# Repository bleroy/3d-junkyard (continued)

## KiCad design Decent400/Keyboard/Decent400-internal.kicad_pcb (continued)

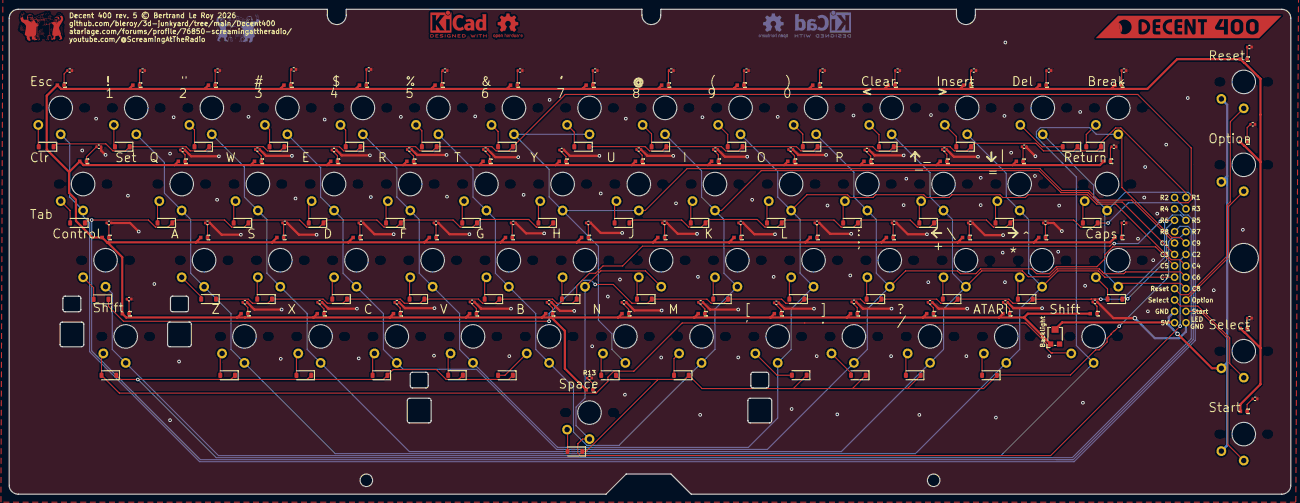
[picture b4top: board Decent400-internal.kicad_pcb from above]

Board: 2 copper layers, 286.0 x 108.2 mm, 180 parts (1 on the bottom side), 142 nets.

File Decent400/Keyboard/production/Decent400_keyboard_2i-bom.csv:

Designator,Footprint,Quantity,Value,LCSC Part #
"D1, D10, D11, D12, D13, D14, D15, D16, D17, D18, D19, D2, D20, D21, D22, D23, D24, D25, D26, D27, D28, D29, D3, D30, D31, D32, D33, D34, D35, D36, D37, D38, D39, D4, D40, D41, D42, D43, D44, D45, D46, D47, D48, D49, D5, D50, D51, D52, D53, D54, D55, D56, D6, D7, D8, D9",D_SOD-123,56,1N4148W,C81598
J1,PinHeader_1x22_P2.54mm_Vertical,1,Conn_01x22,
"R1, R10, R11, R12, R13, R14, R15, R16, R17, R18, R19, R2, R20, R21, R22, R23, R24, R25, R26, R27, R28, R29, R3, R30, R31, R32, R33, R34, R35, R36, R37, R38, R39, R4, R40, R41, R42, R43, R44, R45, R46, R47, R48, R49, R5, R50, R51, R52, R53, R54, R55, R56, R57, R58, R6, R61, R62, R63, R64, R7, R8, R9",0603,62,100,C22775
RV1,Potentiometer_Bourns_TC33X_Vertical,1,R_Potentiometer,C720647
SW0,MX-1-00U-LED-UPSIDE-DOWN,1,0,C193191
SW1,MX-1-00U-LED-UPSIDE-DOWN,1,1,C193191
SW2,MX-1-00U-LED-UPSIDE-DOWN,1,2,C193191
SW3,MX-1-00U-LED-UPSIDE-DOWN,1,3,C193191
SW4,MX-1-00U-LED-UPSIDE-DOWN,1,4,C193191
SW5,MX-1-00U-LED-UPSIDE-DOWN,1,5,C193191
SW6,MX-1-00U-LED-UPSIDE-DOWN,1,6,C193191
SW7,MX-1-00U-LED-UPSIDE-DOWN,1,7,C193191
SW8,MX-1-00U-LED-UPSIDE-DOWN,1,8,C193191
SW9,MX-1-00U-LED-UPSIDE-DOWN,1,9,C193191
SWA1,MX-1-00U-LED-UPSIDE-DOWN,1,A,C193191
SWB1,MX-1-00U-LED-UPSIDE-DOWN,1,B,C193191
SWBrk1,MX-1-25U-LED-REVERSED,1,Break,C193191
SWC1,MX-1-00U-LED-UPSIDE-DOWN,1,C,C193191
SWComma1,MX-1-00U-LED-UPSIDE-DOWN,1,Comma,C193191
SWCps1,MX-1-00U-LED-UPSIDE-DOWN,1,Caps,C193191
"SWCtl1, SWCtl2",MX-1-25U-LED-REVERSED,2,Control,C193191
SWD1,MX-1-00U-LED-UPSIDE-DOWN,1,D,C193191
SWDash1,MX-1-00U-LED-UPSIDE-DOWN,1,Dash,C193191
SWDel1,MX-1-75U-LED-REVERSED,1,Del,C193191
SWE1,MX-1-00U-LED-UPSIDE-DOWN,1,E,C193191
SWEqual1,MX-1-00U-LED-UPSIDE-DOWN,1,Equal,C193191
SWEsc1,MX-1-25U-LED-REVERSED,1,Esc,C193191
SWF1,MX-1-00U-LED-UPSIDE-DOWN,1,F,C193191
SWG1,MX-1-00U-LED-UPSIDE-DOWN,1,G,C193191
SWGT1,MX-1-00U-LED-UPSIDE-DOWN,1,GreaterThan,C193191
SWH1,MX-1-00U-LED-UPSIDE-DOWN,1,H,C193191
SWI1,MX-1-00U-LED-UPSIDE-DOWN,1,I,C193191
SWInv1,MX-1-00U-LED-UPSIDE-DOWN,1,Atari,C193191
SWJ1,MX-1-00U-LED-UPSIDE-DOWN,1,J,C193191
SWK1,MX-1-00U-LED-UPSIDE-DOWN,1,K,C193191
SWL1,MX-1-00U-LED-UPSIDE-DOWN,1,L,C193191
SWLT1,MX-1-00U-LED-UPSIDE-DOWN,1,LessThan,C193191
SWLeftSft1,MX-1-25U-LED-REVERSED,1,Shift,C193191
SWM1,MX-1-00U-LED-UPSIDE-DOWN,1,M,C193191
SWN1,MX-1-00U-LED-UPSIDE-DOWN,1,N,C193191
SWO1,MX-1-00U-LED-UPSIDE-DOWN,1,O,C193191
SWOption1,MX-1-00U-LED,1,Option,C193191
SWP1,MX-1-00U-LED-UPSIDE-DOWN,1,P,C193191
SWPeriod1,MX-1-00U-LED-UPSIDE-DOWN,1,Period,C193191
SWPlus1,MX-1-00U-LED-UPSIDE-DOWN,1,Plus,C193191
SWQ1,MX-1-00U-LED-UPSIDE-DOWN,1,Q,C193191
SWR1,MX-1-00U-LED-UPSIDE-DOWN,1,R,C193191
SWReset1,MX-1-00U-LED,1,Reset,C193191
SWRet1,MX-1-25U-LED-REVERSED,1,Return,C193191
SWRightSft1,MX-2-25U-LED-REVERSED,1,Shift,C193191
SWS1,MX-1-00U-LED-UPSIDE-DOWN,1,S,C193191
SWSelect1,MX-1-00U-LED,1,Select,C193191
SWSemi1,MX-1-00U-LED-UPSIDE-DOWN,1,Semicolon,C193191
SWSlash1,MX-1-00U-LED-UPSIDE-DOWN,1,Slash,C193191
SWSpc1,MX-6-25U-LED-REVERSED,1,Space,C193191
SWStar1,MX-1-00U-LED-UPSIDE-DOWN,1,Star,C193191
SWStart1,MX-1-00U-LED,1,Start,C193191
SWT1,MX-1-00U-LED-UPSIDE-DOWN,1,T,C193191
SWTab1,MX-1-25U-LED-REVERSED,1,Tab,C193191
SWU1,MX-1-00U-LED-UPSIDE-DOWN,1,U,C193191
SWV1,MX-1-00U-LED-UPSIDE-DOWN,1,V,C193191
SWW1,MX-1-00U-LED-UPSIDE-DOWN,1,W,C193191
SWX1,MX-1-00U-LED-UPSIDE-DOWN,1,X,C193191
SWY1,MX-1-00U-LED-UPSIDE-DOWN,1,Y,C193191
SWZ1,MX-1-00U-LED-UPSIDE-DOWN,1,Z,C193191

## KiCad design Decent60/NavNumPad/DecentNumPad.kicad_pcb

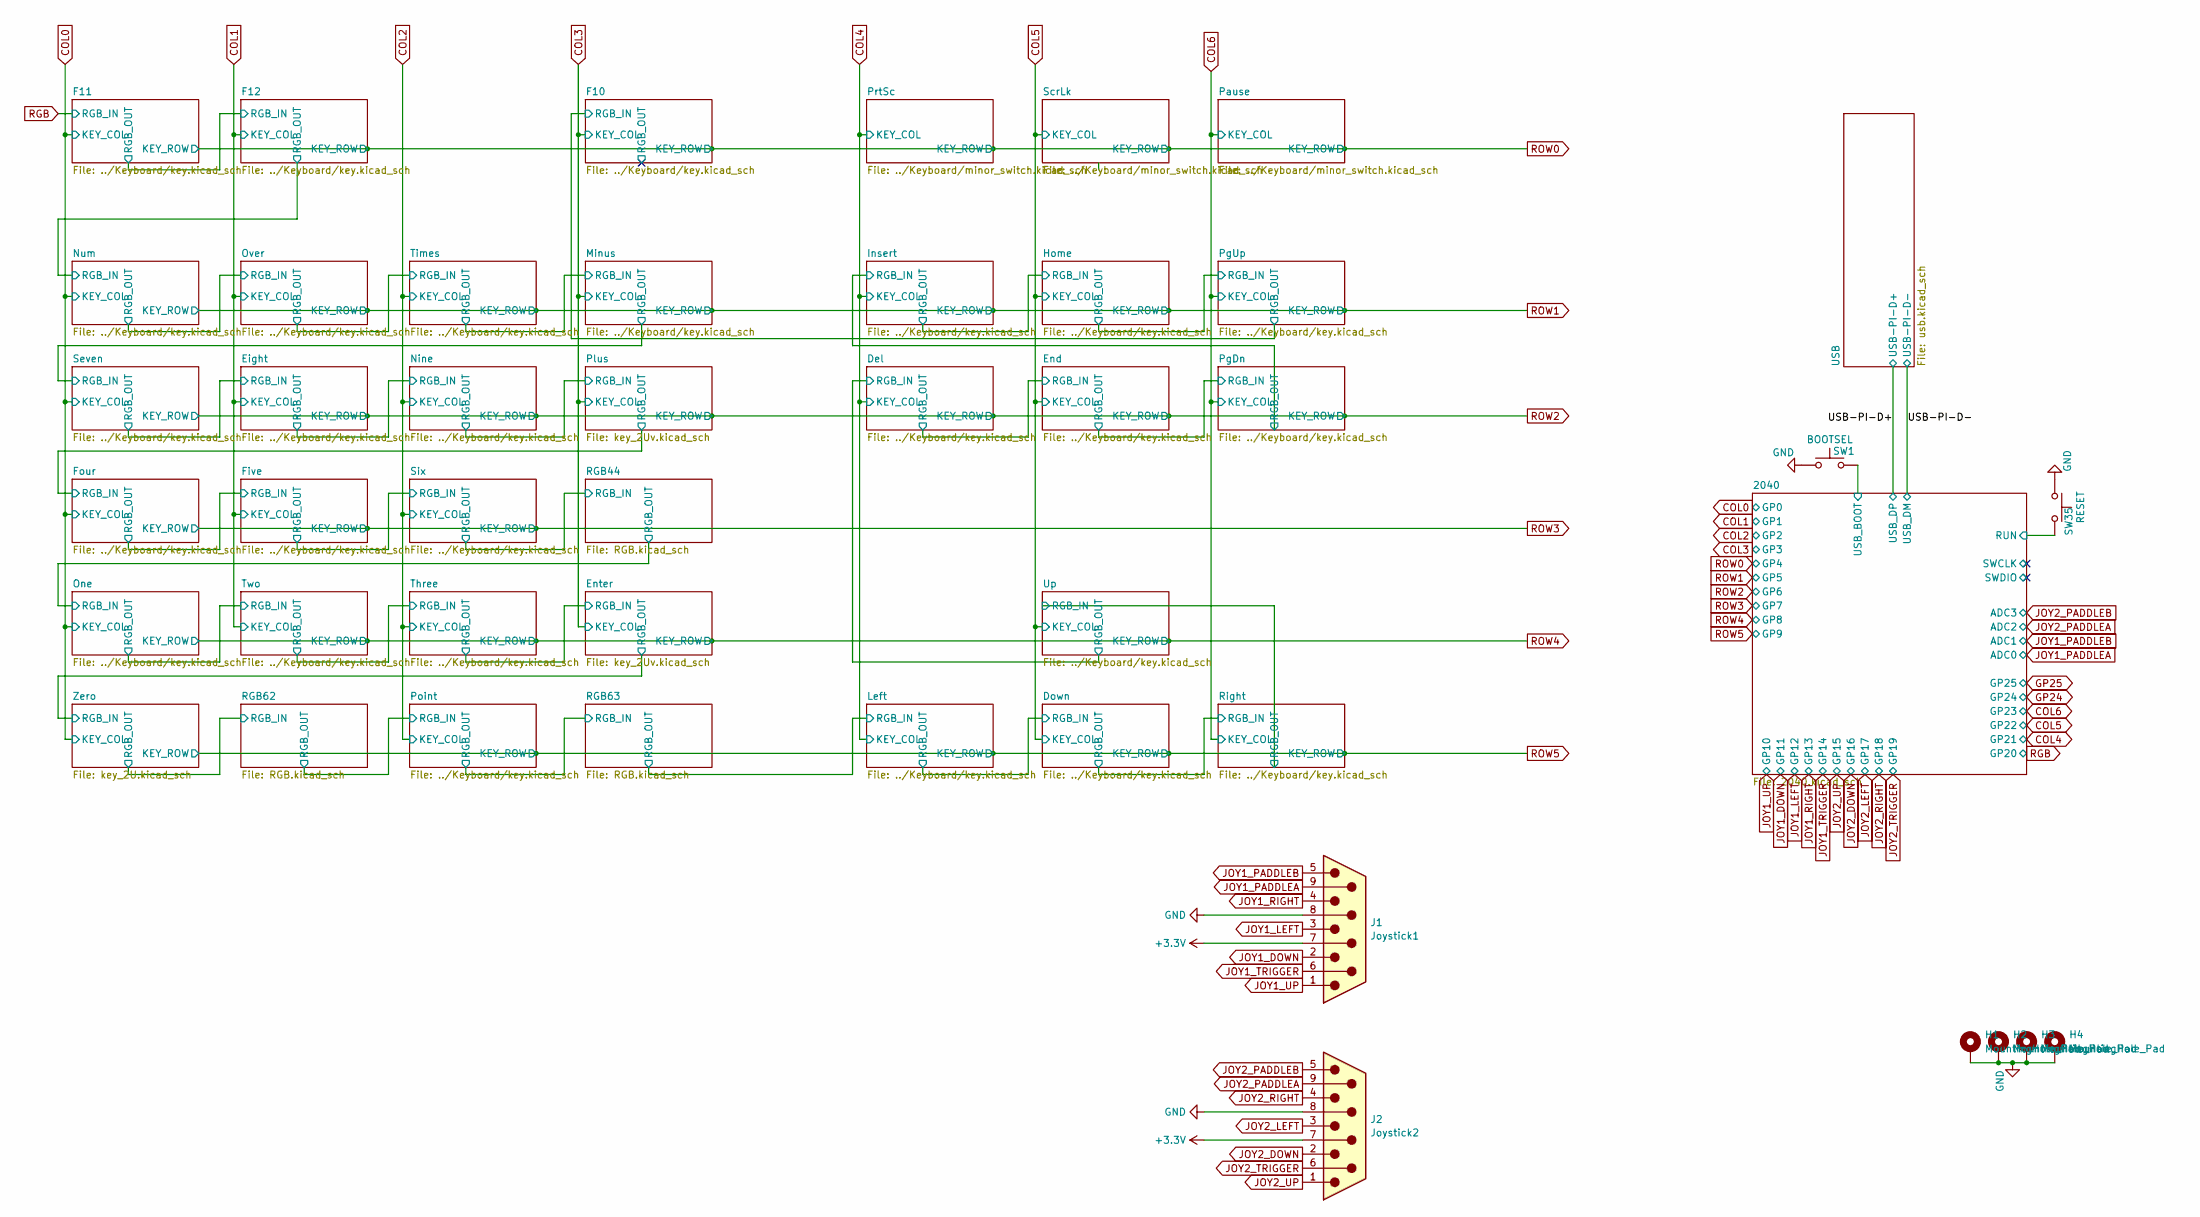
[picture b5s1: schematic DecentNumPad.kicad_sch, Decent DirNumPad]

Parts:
H1, H2, H3, H4: MountingHole_Pad; MountingHole_2.5mm_Pad_Via
J1: Joystick1; DSUB-9_Pins_Horizontal_P2.77x2.84mm_EdgePinOffset4.94mm_Hou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
J2: Joystick2; DSUB-9_Pins_Horizontal_P2.77x2.84mm_EdgePinOffset4.94mm_Hou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
SW1: BOOTSEL; SW-SMD_L3.9-W3.0-P4.45; LCSC Part # C720477
SW35: RESET; SW-SMD_L3.9-W3.0-P4.45; LCSC Part # C720477

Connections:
+3.3V: J1.7, J2.7; also elsewhere on the board
/2040/RUN: SW35.2; also elsewhere on the board
/2040/USB_BOOT: SW1.2; also elsewhere on the board
GND: H1.1 (1_1), H2.1 (1_1), H3.1 (1_1), H4.1 (1_1), J1.8, J2.8, SW1.1, SW35.1; also elsewhere on the board
JOY1_DOWN: J1.2; also elsewhere on the board
JOY1_LEFT: J1.3; also elsewhere on the board
JOY1_PADDLEA: J1.9; also elsewhere on the board
JOY1_PADDLEB: J1.5; also elsewhere on the board
JOY1_RIGHT: J1.4; also elsewhere on the board
JOY1_TRIGGER: J1.6; also elsewhere on the board
JOY1_UP: J1.1; also elsewhere on the board
JOY2_DOWN: J2.2; also elsewhere on the board
JOY2_LEFT: J2.3; also elsewhere on the board
JOY2_PADDLEA: J2.9; also elsewhere on the board
JOY2_PADDLEB: J2.5; also elsewhere on the board
JOY2_RIGHT: J2.4; also elsewhere on the board
JOY2_TRIGGER: J2.6; also elsewhere on the board
JOY2_UP: J2.1; also elsewhere on the board

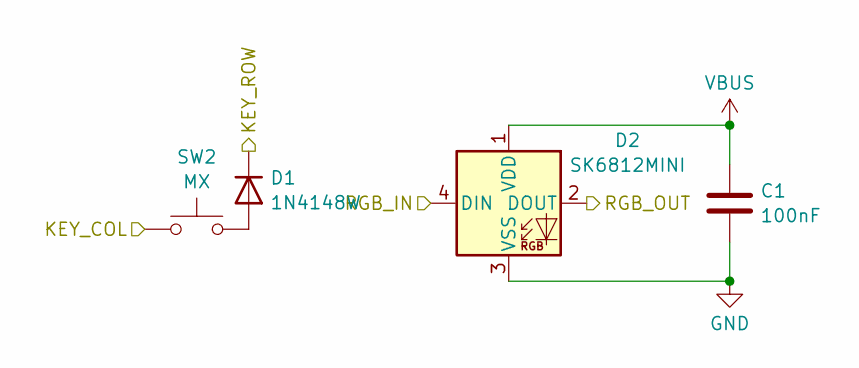
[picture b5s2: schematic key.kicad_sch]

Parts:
C1: 100nF; C_0402_1005Metric; LCSC Part # C1525
D1: 1N4148W; D_SOD-123; LCSC Part # C81598
D2: SK6812MINI; LED_SK6812MINI-E_3.2x2.8mm_P1.5mm_ReverseMount; LCSC Part # C5378731
SW2: MX; SMD_KEYBOARD-SW; LCSC Part # C41430893

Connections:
/F11/RGB_OUT: D2.2 (DOUT); also elsewhere on the board
COL0: SW2.1; also elsewhere on the board
GND: C1.2, D2.3 (VSS); also elsewhere on the board
unnamed: D1.2 (A), SW2.2
RGB: D2.4 (DIN); also elsewhere on the board
ROW0: D1.1 (K); also elsewhere on the board
VBUS: C1.1, D2.1 (VDD); also elsewhere on the board

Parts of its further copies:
C2, C3, C4, C5, C6, C8, C9, C10, C11, C12, C13, C14, C15, C17, C19, C45, C46, C47, C48, C49, C50, C53, C54, C55, C56, C57: 100nF; C_0402_1005Metric; LCSC Part # C1525
D3, D5, D7, D9, D11, D15, D17, D19, D21, D23, D25, D27, D29, D33, D37, D44, D46, D48, D50, D52, D54, D60, D62, D64, D66, D68: 1N4148W; D_SOD-123; LCSC Part # C81598
D4, D6, D8, D10, D12, D16, D18, D20, D22, D24, D26, D28, D30, D34, D38, D45, D47, D49, D51, D53, D55, D61, D63, D65, D67, D69: SK6812MINI; LED_SK6812MINI-E_3.2x2.8mm_P1.5mm_ReverseMount; LCSC Part # C5378731
SW3, SW4, SW5, SW6, SW7, SW9, SW10, SW11, SW12, SW13, SW14, SW15, SW16, SW18, SW20, SW22, SW23, SW24, SW25, SW26, SW27, SW30, SW31, SW32, SW33, SW34: MX; SMD_KEYBOARD-SW; LCSC Part # C41430893

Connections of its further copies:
/Del/RGB_IN: D51.2 (DOUT), D67.4 (DIN)
/Del/RGB_OUT: D65.4 (DIN), D67.2 (DOUT)
/Down/RGB_IN: D45.2 (DOUT), D47.4 (DIN)
/Down/RGB_OUT: D47.2 (DOUT), D49.4 (DIN)
/Eight/RGB_IN: D16.2 (DOUT), D18.4 (DIN)
/Eight/RGB_OUT: D18.2 (DOUT), D20.4 (DIN)
/End/RGB_OUT: D65.2 (DOUT), D69.4 (DIN)
/Enter/RGB_IN: D30.2 (DOUT); also elsewhere on the board
/F10/RGB_IN: D61.2 (DOUT), D63.4 (DIN)
/F10/RGB_OUT: D63.2 (DOUT)
/F11/RGB_OUT: D4.4 (DIN); also elsewhere on the board
/F12/RGB_OUT: D4.2 (DOUT), D6.4 (DIN)
/Five/RGB_IN: D22.4 (DIN), D28.2 (DOUT)
/Five/RGB_OUT: D22.2 (DOUT), D24.4 (DIN)
/Four/RGB_IN: D28.4 (DIN); also elsewhere on the board
/Home/RGB_IN: D53.2 (DOUT), D55.4 (DIN)
/Home/RGB_OUT: D55.2 (DOUT), D61.4 (DIN)
/Insert/RGB_IN: D53.4 (DIN), D69.2 (DOUT)
/Left/RGB_IN: D45.4 (DIN); also elsewhere on the board
/Minus/RGB_IN: D10.2 (DOUT), D12.4 (DIN)
/Minus/RGB_OUT: D12.2 (DOUT), D16.4 (DIN)
/Nine/RGB_OUT: D20.2 (DOUT); also elsewhere on the board
/Num/RGB_OUT: D6.2 (DOUT), D8.4 (DIN)
/One/RGB_IN: D34.4 (DIN); also elsewhere on the board
/One/RGB_OUT: D26.4 (DIN), D34.2 (DOUT)
/Over/RGB_OUT: D8.2 (DOUT), D10.4 (DIN)
/Point/RGB_IN: D38.4 (DIN); also elsewhere on the board
/Point/RGB_OUT: D38.2 (DOUT); also elsewhere on the board
/RGB44/RGB_IN: D24.2 (DOUT); also elsewhere on the board
/Right/RGB_OUT: D49.2 (DOUT), D51.4 (DIN)
/Three/RGB_IN: D26.2 (DOUT), D30.4 (DIN)
COL0: SW4.1, SW9.1, SW15.1, SW18.1; also elsewhere on the board
COL1: SW3.1, SW5.1, SW10.1, SW12.1, SW14.1; also elsewhere on the board
COL2: SW6.1, SW11.1, SW13.1, SW16.1, SW20.1; also elsewhere on the board
COL3: SW7.1, SW31.1; also elsewhere on the board
COL4: SW22.1, SW26.1, SW33.1; also elsewhere on the board
COL5: SW23.1, SW25.1, SW27.1, SW32.1; also elsewhere on the board
COL6: SW24.1, SW30.1, SW34.1; also elsewhere on the board
GND: C2.2, C3.2, C4.2, C5.2, C6.2, C8.2, C9.2, C10.2, C11.2, C12.2, C13.2, C14.2, C15.2, C17.2, C19.2, C45.2, C46.2, C47.2, C48.2, C49.2, C50.2, C53.2, C54.2, C55.2, C56.2, C57.2, D4.3 (VSS), D6.3 (VSS), D8.3 (VSS), D10.3 (VSS), D12.3 (VSS), D16.3 (VSS), D18.3 (VSS), D20.3 (VSS), D22.3 (VSS), D24.3 (VSS), D26.3 (VSS), D28.3 (VSS), D30.3 (VSS), D34.3 (VSS), D38.3 (VSS), D45.3 (VSS), D47.3 (VSS), D49.3 (VSS), D51.3 (VSS), D53.3 (VSS), D55.3 (VSS), D61.3 (VSS), D63.3 (VSS), D65.3 (VSS), D67.3 (VSS), D69.3 (VSS); also elsewhere on the board
unnamed: D3.2 (A), SW3.2
unnamed: D5.2 (A), SW4.2
unnamed: D7.2 (A), SW5.2
unnamed: D9.2 (A), SW6.2
unnamed: D11.2 (A), SW7.2
unnamed: D15.2 (A), SW9.2
unnamed: D17.2 (A), SW10.2
unnamed: D19.2 (A), SW11.2
unnamed: D21.2 (A), SW12.2
unnamed: D23.2 (A), SW13.2
unnamed: D25.2 (A), SW14.2
unnamed: D27.2 (A), SW15.2
unnamed: D29.2 (A), SW16.2
unnamed: D33.2 (A), SW18.2
unnamed: D37.2 (A), SW20.2
unnamed: D44.2 (A), SW22.2
unnamed: D46.2 (A), SW23.2
unnamed: D48.2 (A), SW24.2
unnamed: D50.2 (A), SW25.2
unnamed: D52.2 (A), SW26.2
unnamed: D54.2 (A), SW27.2
unnamed: D60.2 (A), SW30.2
unnamed: D62.2 (A), SW31.2
unnamed: D64.2 (A), SW32.2
unnamed: D66.2 (A), SW33.2
unnamed: D68.2 (A), SW34.2
ROW0: D3.1 (K), D62.1 (K); also elsewhere on the board
ROW1: D5.1 (K), D7.1 (K), D9.1 (K), D11.1 (K), D52.1 (K), D54.1 (K), D60.1 (K); also elsewhere on the board
ROW2: D15.1 (K), D17.1 (K), D19.1 (K), D64.1 (K), D66.1 (K), D68.1 (K); also elsewhere on the board
ROW3: D21.1 (K), D23.1 (K), D27.1 (K); also elsewhere on the board
ROW4: D25.1 (K), D29.1 (K), D33.1 (K), D50.1 (K); also elsewhere on the board
ROW5: D37.1 (K), D44.1 (K), D46.1 (K), D48.1 (K); also elsewhere on the board
VBUS: C2.1, C3.1, C4.1, C5.1, C6.1, C8.1, C9.1, C10.1, C11.1, C12.1, C13.1, C14.1, C15.1, C17.1, C19.1, C45.1, C46.1, C47.1, C48.1, C49.1, C50.1, C53.1, C54.1, C55.1, C56.1, C57.1, D4.1 (VDD), D6.1 (VDD), D8.1 (VDD), D10.1 (VDD), D12.1 (VDD), D16.1 (VDD), D18.1 (VDD), D20.1 (VDD), D22.1 (VDD), D24.1 (VDD), D26.1 (VDD), D28.1 (VDD), D30.1 (VDD), D34.1 (VDD), D38.1 (VDD), D45.1 (VDD), D47.1 (VDD), D49.1 (VDD), D51.1 (VDD), D53.1 (VDD), D55.1 (VDD), D61.1 (VDD), D63.1 (VDD), D65.1 (VDD), D67.1 (VDD), D69.1 (VDD); also elsewhere on the board

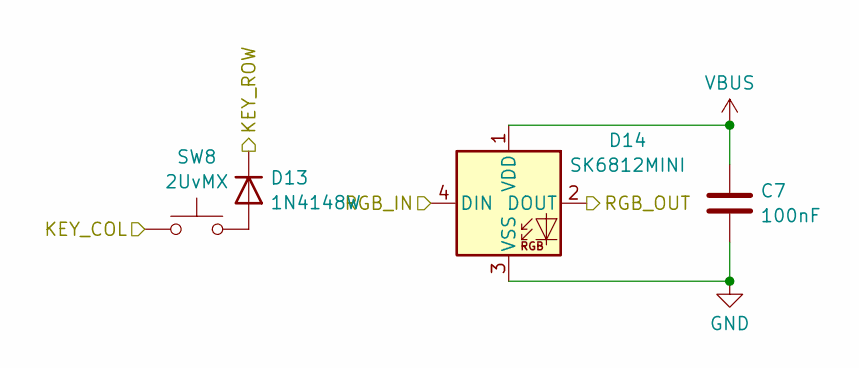
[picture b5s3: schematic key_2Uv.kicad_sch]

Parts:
C7: 100nF; C_0402_1005Metric; LCSC Part # C1525
D13: 1N4148W; D_SOD-123; LCSC Part # C81598
D14: SK6812MINI; LED_SK6812MINI-E_3.2x2.8mm_P1.5mm_ReverseMount; LCSC Part # C5378731
SW8: 2UvMX; Kailh_socket_MX_2-00U_V; LCSC Part # C41430893

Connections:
/Four/RGB_IN: D14.2 (DOUT); also elsewhere on the board
/Nine/RGB_OUT: D14.4 (DIN); also elsewhere on the board
COL3: SW8.1; also elsewhere on the board
GND: C7.2, D14.3 (VSS); also elsewhere on the board
unnamed: D13.2 (A), SW8.2
ROW2: D13.1 (K); also elsewhere on the board
VBUS: C7.1, D14.1 (VDD); also elsewhere on the board

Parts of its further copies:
C16: 100nF; C_0402_1005Metric; LCSC Part # C1525
D31: 1N4148W; D_SOD-123; LCSC Part # C81598
D32: SK6812MINI; LED_SK6812MINI-E_3.2x2.8mm_P1.5mm_ReverseMount; LCSC Part # C5378731
SW17: 2UvMX; Kailh_socket_MX_2-00U_V; LCSC Part # C41430893

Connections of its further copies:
/Enter/RGB_IN: D32.4 (DIN); also elsewhere on the board
/Enter/RGB_OUT: D32.2 (DOUT); also elsewhere on the board
COL3: SW17.1; also elsewhere on the board
GND: C16.2, D32.3 (VSS); also elsewhere on the board
unnamed: D31.2 (A), SW17.2
ROW4: D31.1 (K); also elsewhere on the board
VBUS: C16.1, D32.1 (VDD); also elsewhere on the board

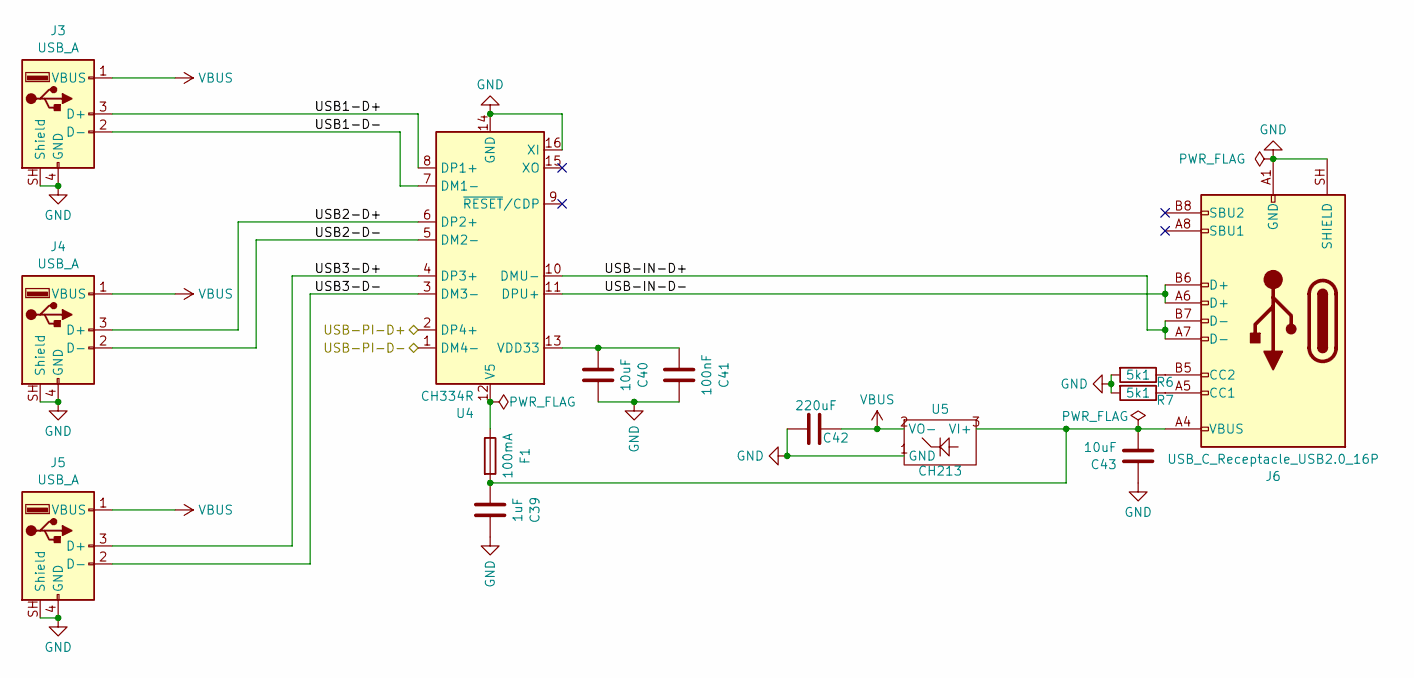
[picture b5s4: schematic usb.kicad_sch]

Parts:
C39: 1uF; C_0402_1005Metric; LCSC Part # C52923
C40, C43: 10uF; C_0402_1005Metric; LCSC Part # C15525
C41: 100nF; C_0402_1005Metric; LCSC Part # C1525
C42: 220uF; CP_Elec_6.3x5.4; LCSC Part # C3345
F1: 100mA; Fuse_1206_3216Metric; LCSC Part # C269108
J3, J4, J5: USB_A; USB_A_Molex_67643_Horizontal
J6: USB_C_Receptacle_USB2.0_16P; USB_C_Receptacle_HCTL_HC-TYPE-C-16P-01A; LCSC Part # C709357
R6, R7: 5k1; R_0402_1005Metric; LCSC Part # C25905
U4: CH334R; QSOP-16_3.9x4.9mm_P0.635mm; LCSC Part # C4154405
U5: CH213; TSOT-23; LCSC Part # C5456874

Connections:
/USB-PI-D+: U4.2 (DP4+); also elsewhere on the board
/USB-PI-D-: U4.1 (DM4-); also elsewhere on the board
/USB/USB1-D+: J3.3 (D+), U4.8 (DP1+)
/USB/USB1-D-: J3.2 (D-), U4.7 (DM1-)
/USB/USB2-D+: J4.3 (D+), U4.6 (DP2+)
/USB/USB2-D-: J4.2 (D-), U4.5 (DM2-)
/USB/USB3-D+: J5.3 (D+), U4.4 (DP3+)
/USB/USB3-D-: J5.2 (D-), U4.3 (DM3-)
/USB/USB-IN-D+: J6.A7 (D-), J6.B7 (D-), U4.10 (DMU-)
/USB/USB-IN-D-: J6.A6 (D+), J6.B6 (D+), U4.11 (DPU+)
GND: C39.2, C40.2, C41.2, C42.2, C43.1, J3.4 (GND), J3.SH (Shield), J4.4 (GND), J4.SH (Shield), J5.4 (GND), J5.SH (Shield), J6.A1 (GND), J6.A12 (GND), J6.B1 (GND), J6.B12 (GND), J6.SH (SHIELD), R6.2, R7.2, U4.14 (GND), U4.16 (XI), U5.1 (GND); also elsewhere on the board
unnamed: J6.A5 (CC1), R7.1
unnamed: J6.B5 (CC2), R6.1
unnamed: F1.1, U4.12 (V5)
unnamed: C40.1, C41.1, U4.13 (VDD33)
unnamed: C39.1, C43.2, F1.2, J6.A4 (VBUS), J6.A9 (VBUS), J6.B4 (VBUS), J6.B9 (VBUS), U5.3 (VI+)
VBUS: C42.1, J3.1 (VBUS), J4.1 (VBUS), J5.1 (VBUS), U5.2 (VO-); also elsewhere on the board

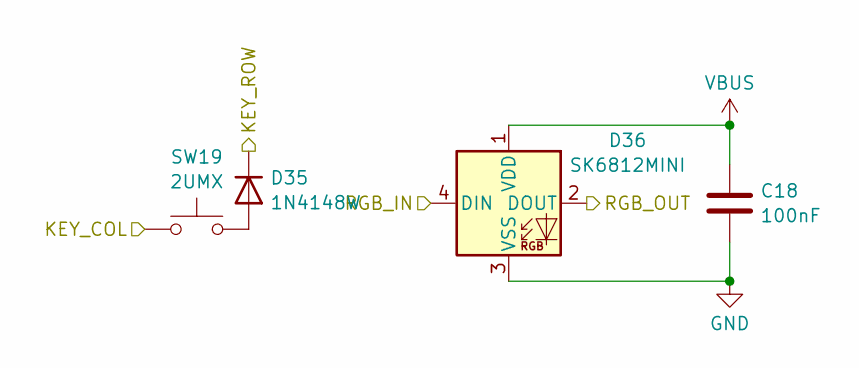
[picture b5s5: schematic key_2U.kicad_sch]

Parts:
C18: 100nF; C_0402_1005Metric; LCSC Part # C1525
D35: 1N4148W; D_SOD-123; LCSC Part # C81598
D36: SK6812MINI; LED_SK6812MINI-E_3.2x2.8mm_P1.5mm_ReverseMount; LCSC Part # C5378731
SW19: 2UMX; Kailh_socket_MX_2-00U; LCSC Part # C41430893

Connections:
/Enter/RGB_OUT: D36.4 (DIN); also elsewhere on the board
/RGB62/RGB_IN: D36.2 (DOUT); also elsewhere on the board
COL0: SW19.1; also elsewhere on the board
GND: C18.2, D36.3 (VSS); also elsewhere on the board
unnamed: D35.2 (A), SW19.2
ROW5: D35.1 (K); also elsewhere on the board
VBUS: C18.1, D36.1 (VDD); also elsewhere on the board

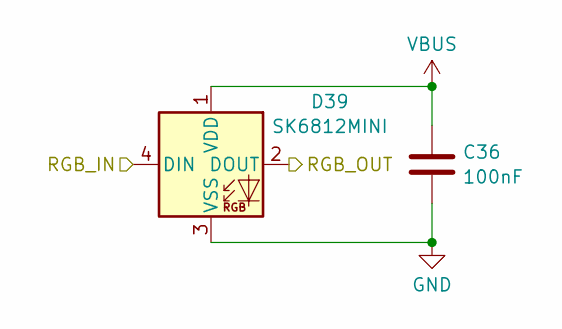
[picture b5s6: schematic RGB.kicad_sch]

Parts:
C36: 100nF; C_0402_1005Metric; LCSC Part # C1525
D39: SK6812MINI; LED_SK6812MINI-E_3.2x2.8mm_P1.5mm_ReverseMount; LCSC Part # C5378731

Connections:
/One/RGB_IN: D39.2 (DOUT); also elsewhere on the board
/RGB44/RGB_IN: D39.4 (DIN); also elsewhere on the board
GND: C36.2, D39.3 (VSS); also elsewhere on the board
VBUS: C36.1, D39.1 (VDD); also elsewhere on the board

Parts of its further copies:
C37, C38: 100nF; C_0402_1005Metric; LCSC Part # C1525
D40, D41: SK6812MINI; LED_SK6812MINI-E_3.2x2.8mm_P1.5mm_ReverseMount; LCSC Part # C5378731

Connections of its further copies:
/Left/RGB_IN: D41.2 (DOUT); also elsewhere on the board
/Point/RGB_IN: D40.2 (DOUT); also elsewhere on the board
/Point/RGB_OUT: D41.4 (DIN); also elsewhere on the board
/RGB62/RGB_IN: D40.4 (DIN); also elsewhere on the board
GND: C37.2, C38.2, D40.3 (VSS), D41.3 (VSS); also elsewhere on the board
VBUS: C37.1, C38.1, D40.1 (VDD), D41.1 (VDD); also elsewhere on the board

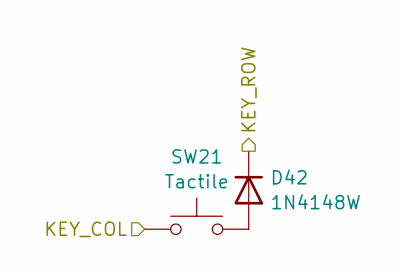
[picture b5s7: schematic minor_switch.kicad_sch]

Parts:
D42: 1N4148W; D_SOD-123; LCSC Part # C81598
SW21: Tactile; SMD_KEYBOARD-SW; LCSC Part # C41430893

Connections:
COL4: SW21.1; also elsewhere on the board
unnamed: D42.2 (A), SW21.2
ROW0: D42.1 (K); also elsewhere on the board

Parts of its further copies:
D56, D58: 1N4148W; D_SOD-123; LCSC Part # C81598
SW28, SW29: Tactile; SMD_KEYBOARD-SW; LCSC Part # C41430893

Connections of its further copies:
COL5: SW28.1; also elsewhere on the board
COL6: SW29.1; also elsewhere on the board
unnamed: D56.2 (A), SW28.2
unnamed: D58.2 (A), SW29.2
ROW0: D56.1 (K), D58.1 (K); also elsewhere on the board

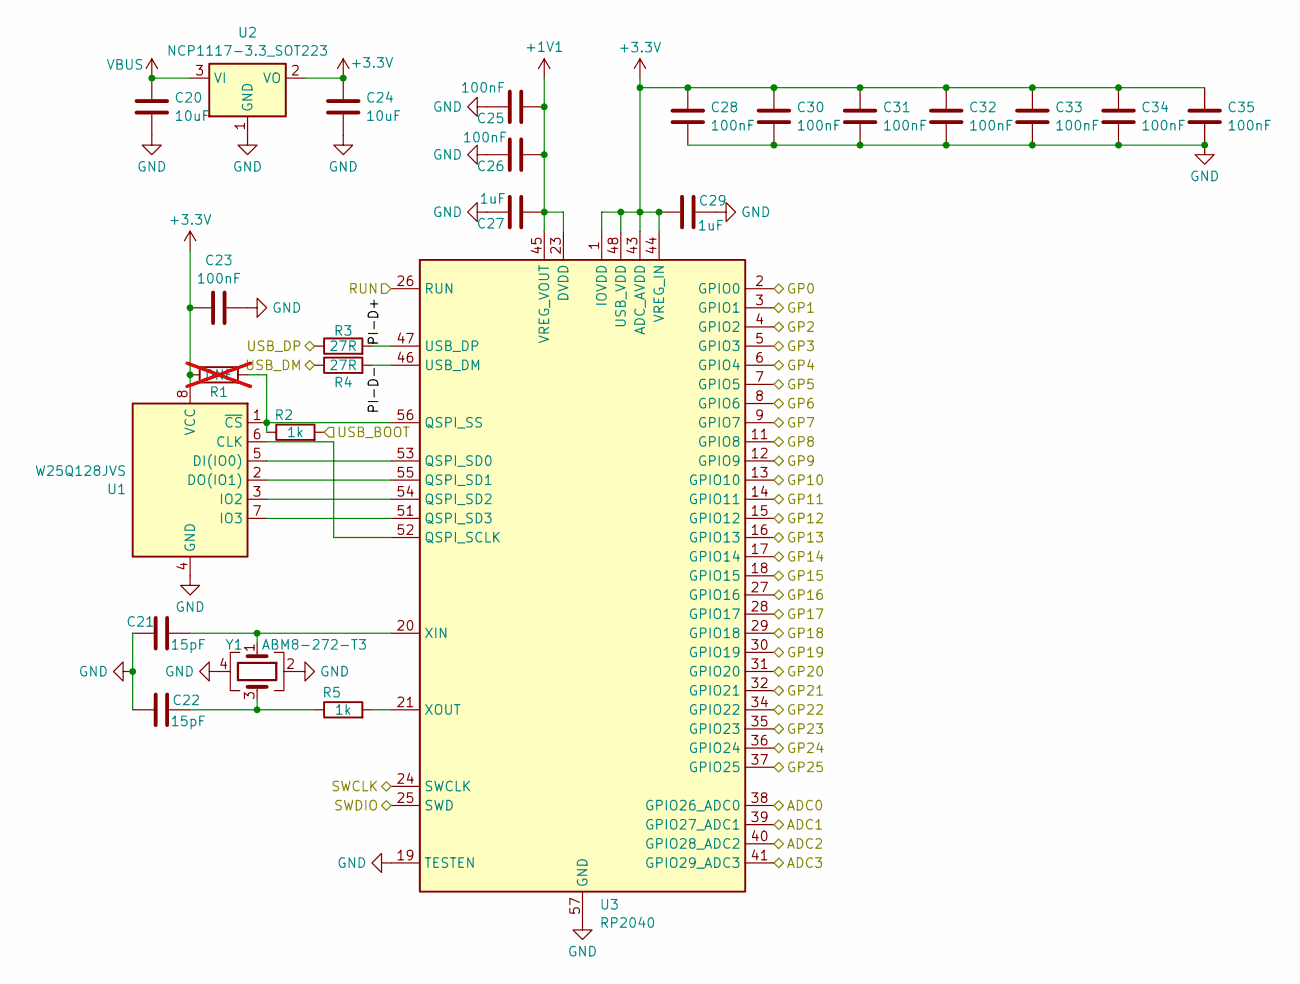
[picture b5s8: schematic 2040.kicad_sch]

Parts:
C20, C24: 10uF; C_0402_1005Metric; LCSC Part # C15525
C21, C22: 15pF; C_0402_1005Metric; LCSC Part # C1548
C23, C25, C26, C28, C30, C31, C32, C33, C34, C35: 100nF; C_0402_1005Metric; LCSC Part # C1525
C27, C29: 1uF; C_0402_1005Metric; LCSC Part # C52923
R1: DNF; R_0402_1005Metric; not fitted
R2, R5: 1k; R_0402_1005Metric; LCSC Part # C11702
R3, R4: 27R; R_0402_1005Metric; LCSC Part # C25100
U1: W25Q128JVS; SOIC-8_5.3x5.3mm_P1.27mm; LCSC Part # C97521
U2: NCP1117-3.3_SOT223; SOT-223-3_TabPin2; LCSC Part # C146799
U3: RP2040; QFN-56-1EP_7x7mm_P0.4mm_EP3.2x3.2mm; LCSC Part # C2040
Y1: ABM8-272-T3; Oscillator_SMD_Abracon_ASE-4Pin_3.2x2.5mm; LCSC Part # C20625731

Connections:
+1V1: C25.1, C26.1, C27.1, U3.23 (DVDD), U3.45 (VREG_VOUT), U3.50 (DVDD)
+3.3V: C23.2, C24.1, C28.1, C29.1, C30.1, C31.1, C32.1, C33.1, C34.1, C35.1, R1.1, U1.8 (VCC), U2.2 (VO), U3.1 (IOVDD), U3.10 (IOVDD), U3.22 (IOVDD), U3.33 (IOVDD), U3.42 (IOVDD), U3.43 (ADC_AVDD), U3.44 (VREG_IN), U3.48 (USB_VDD), U3.49 (IOVDD); also elsewhere on the board
/2040/PI-D+: R3.2, U3.47 (USB_DP)
/2040/PI-D-: R4.2, U3.46 (USB_DM)
/2040/RUN: U3.26 (RUN); also elsewhere on the board
/2040/SWCLK: U3.24 (SWCLK)
/2040/SWDIO: U3.25 (SWD)
/2040/USB_BOOT: R2.2; also elsewhere on the board
/USB-PI-D+: R3.1; also elsewhere on the board
/USB-PI-D-: R4.1; also elsewhere on the board
COL0: U3.2 (GPIO0); also elsewhere on the board
COL1: U3.3 (GPIO1); also elsewhere on the board
COL2: U3.4 (GPIO2); also elsewhere on the board
COL3: U3.5 (GPIO3); also elsewhere on the board
COL4: U3.32 (GPIO21); also elsewhere on the board
COL5: U3.34 (GPIO22); also elsewhere on the board
COL6: U3.35 (GPIO23); also elsewhere on the board
GND: C20.2, C21.1, C22.1, C23.1, C24.2, C25.2, C26.2, C27.2, C28.2, C29.2, C30.2, C31.2, C32.2, C33.2, C34.2, C35.2, U1.4 (GND), U2.1 (GND), U3.19 (TESTEN), U3.57 (GND), Y1.2, Y1.4; also elsewhere on the board
GP24: U3.36 (GPIO24)
GP25: U3.37 (GPIO25)
JOY1_DOWN: U3.14 (GPIO11); also elsewhere on the board
JOY1_LEFT: U3.15 (GPIO12); also elsewhere on the board
JOY1_PADDLEA: U3.38 (GPIO26_ADC0); also elsewhere on the board
JOY1_PADDLEB: U3.39 (GPIO27_ADC1); also elsewhere on the board
JOY1_RIGHT: U3.16 (GPIO13); also elsewhere on the board
JOY1_TRIGGER: U3.17 (GPIO14); also elsewhere on the board
JOY1_UP: U3.13 (GPIO10); also elsewhere on the board
JOY2_DOWN: U3.27 (GPIO16); also elsewhere on the board
JOY2_LEFT: U3.28 (GPIO17); also elsewhere on the board
JOY2_PADDLEA: U3.40 (GPIO28_ADC2); also elsewhere on the board
JOY2_PADDLEB: U3.41 (GPIO29_ADC3); also elsewhere on the board
JOY2_RIGHT: U3.29 (GPIO18); also elsewhere on the board
JOY2_TRIGGER: U3.30 (GPIO19); also elsewhere on the board
JOY2_UP: U3.18 (GPIO15); also elsewhere on the board
unnamed: C22.2, R5.1, Y1.3
unnamed: U1.6 (CLK), U3.52 (QSPI_SCLK)
unnamed: U1.5 (DI(IO0)), U3.53 (QSPI_SD0)
unnamed: U1.2 (DO(IO1)), U3.55 (QSPI_SD1)
unnamed: U1.3 (IO2), U3.54 (QSPI_SD2)
unnamed: U1.7 (IO3), U3.51 (QSPI_SD3)
unnamed: R1.2, R2.1, U1.1 (~CS), U3.56 (QSPI_SS)
unnamed: C21.2, U3.20 (XIN), Y1.1
unnamed: R5.2, U3.21 (XOUT)
RGB: U3.31 (GPIO20); also elsewhere on the board
ROW0: U3.6 (GPIO4); also elsewhere on the board
ROW1: U3.7 (GPIO5); also elsewhere on the board
ROW2: U3.8 (GPIO6); also elsewhere on the board
ROW3: U3.9 (GPIO7); also elsewhere on the board
ROW4: U3.11 (GPIO8); also elsewhere on the board
ROW5: U3.12 (GPIO9); also elsewhere on the board
VBUS: C20.1, U2.3 (VI); also elsewhere on the board

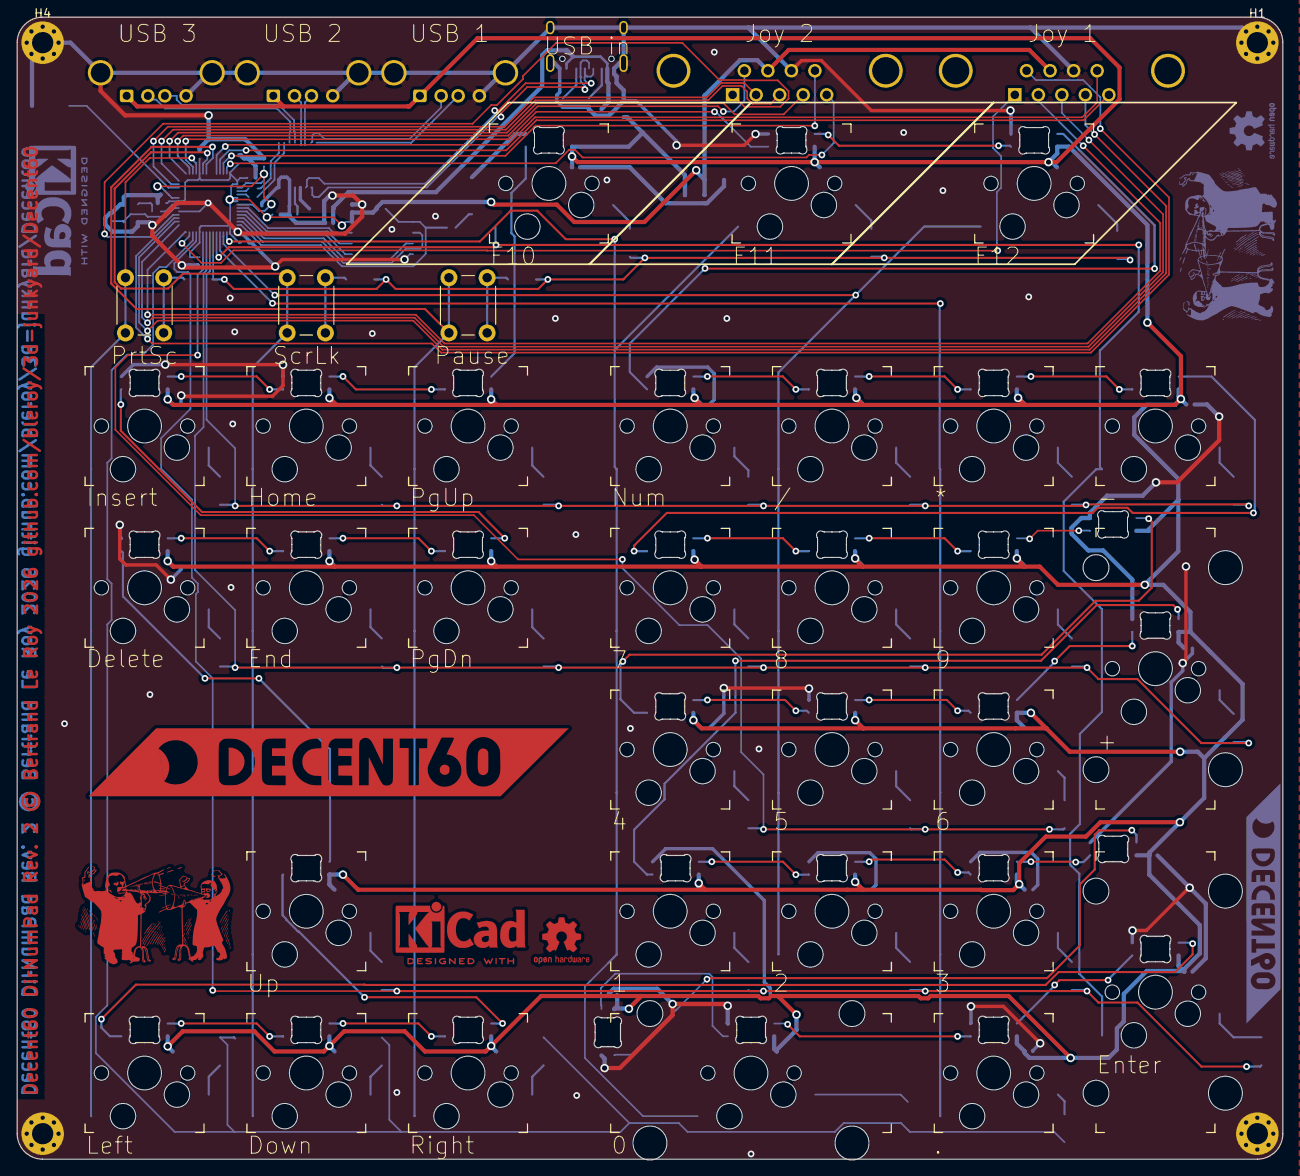
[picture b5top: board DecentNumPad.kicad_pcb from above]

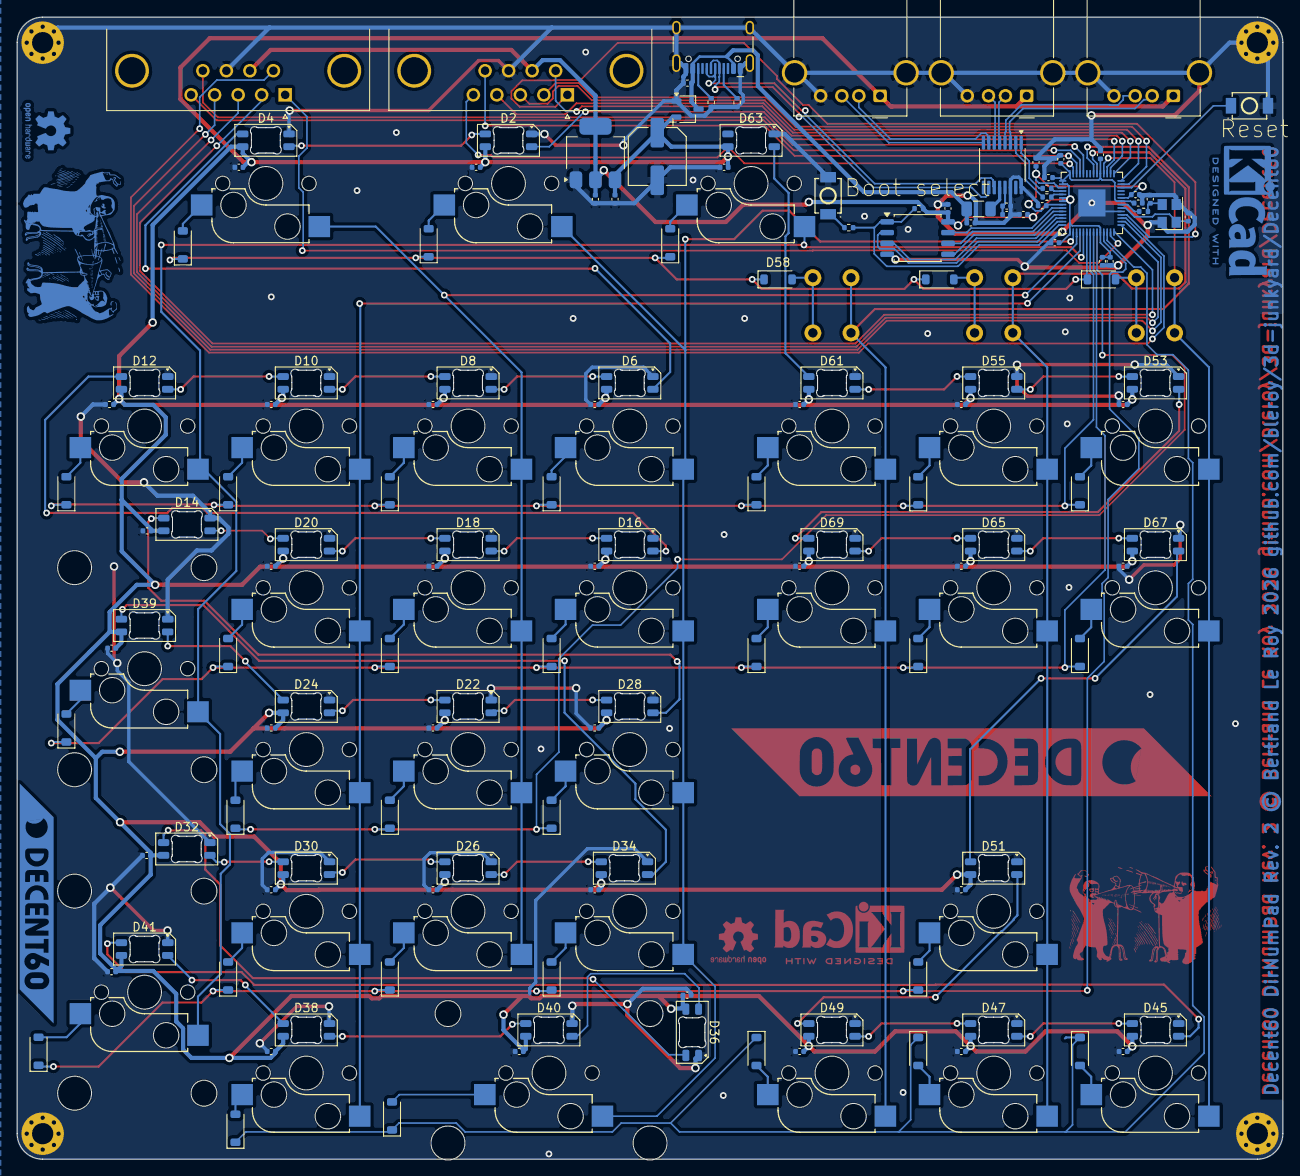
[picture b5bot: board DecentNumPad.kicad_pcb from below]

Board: 2 copper layers, 149.1 x 134.5 mm, 179 parts (142 on the bottom side), 125 nets.

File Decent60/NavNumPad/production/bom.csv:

Designator,Footprint,Quantity,Value,LCSC Part #
"C1, C10, C11, C12, C13, C14, C15, C16, C17, C18, C19, C2, C23, C25, C26, C28, C3, C30, C31, C32, C33, C34, C35, C36, C37, C38, C4, C41, C45, C46, C47, C48, C49, C5, C50, C53, C54, C55, C56, C57, C6, C7, C8, C9",0402,44,100nF,C1525
"C20, C24, C40, C43",0402,4,10uF,C15525
"C21, C22",0402,2,15pF,C1548
"C27, C29, C39",0402,3,1uF,C52923
C42,CP_Elec_6.3x5.4,1,220uF,C3345
"D1, D11, D13, D15, D17, D19, D21, D23, D25, D27, D29, D3, D31, D33, D35, D37, D42, D44, D46, D48, D5, D50, D52, D54, D56, D58, D60, D62, D64, D66, D68, D7, D9",D_SOD-123,33,1N4148W,C81598
"D10, D12, D14, D16, D18, D2, D20, D22, D24, D26, D28, D30, D32, D34, D36, D38, D39, D4, D40, D41, D45, D47, D49, D51, D53, D55, D6, D61, D63, D65, D67, D69, D8",LED_SK6812MINI-E_3.2x2.8mm_P1.5mm_ReverseMount,33,SK6812MINI,C5378731
F1,1206,1,100mA,C269108
J6,USB_C_Receptacle_HCTL_HC-TYPE-C-16P-01A,1,USB_C_Receptacle_USB2.0_16P,C709357
"R2, R5",0402,2,1k,C11702
"R3, R4",0402,2,27R,C25100
"R6, R7",0402,2,5k1,C25905
SW1,SW-SMD_L3.9-W3.0-P4.45,1,BOOTSEL,C720477
"SW10, SW11, SW12, SW13, SW14, SW15, SW16, SW18, SW2, SW20, SW22, SW23, SW24, SW25, SW26, SW27, SW3, SW30, SW31, SW32, SW33, SW34, SW4, SW5, SW6, SW7, SW9",Kailh_socket_MX_1-00U,27,MX,C41430893
"SW17, SW8",Kailh_socket_MX_2-00U_V,2,2UvMX,C41430893
SW19,Kailh_socket_MX_2-00U,1,2UMX,C41430893
SW35,SW-SMD_L3.9-W3.0-P4.45,1,RESET,C720477
U1,SOIC-8_5.3x5.3mm_P1.27mm,1,W25Q128JVS,C97521
U2,SOT-223-3_TabPin2,1,NCP1117-3.3_SOT223,C146799
U3,QFN-56-1EP_7x7mm_P0.4mm_EP3.2x3.2mm,1,RP2040,C2040
U4,QSOP-16_3.9x4.9mm_P0.635mm,1,CH334R,C4154405
U5,TSOT-23,1,CH213,C5456874
Y1,Oscillator_SMD_Abracon_ASE-4Pin_3.2x2.5mm,1,ABM8-272-T3,C20625731
